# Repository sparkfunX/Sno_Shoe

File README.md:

# Snō Shoe

A Qwiic, USB-C and HDMI breakout board for the [Alorium Technology Snō](https://www.sparkfun.com/products/15145)

The Alorium Technologies Snō is based on the Intel MAX 10 10M16SAU169C8G FPGA. It includes an ATmega328-compatible microcontroller core
which appears as an Arduino Uno and can be configured as normal through the Arduino IDE. It supports Serial, I<sup>2</sup>C and all the usual
Uno features.

The Snō Shoe makes it easy to connect to the Snō over:
- USB-C (instead of needing to use an FTDI adapter)
- HDMI
- Qwiic (I<sup>2</sup>C)

Paul has written an "Xcelerator Block" for the Snō which produces VGA text and graphics over HDMI. The assembled Snō Shoe is essentially an
Arduino-programmable Serial & Qwiic VGA Adapter.

- https://github.com/PaulZC/XLR8_VGA_HDMI_XB

## Repository Contents

- **/Hardware** - Eagle PCB, SCH and LBR design files
- **[LICENSE.md](./LICENSE.md)** contains the licence information

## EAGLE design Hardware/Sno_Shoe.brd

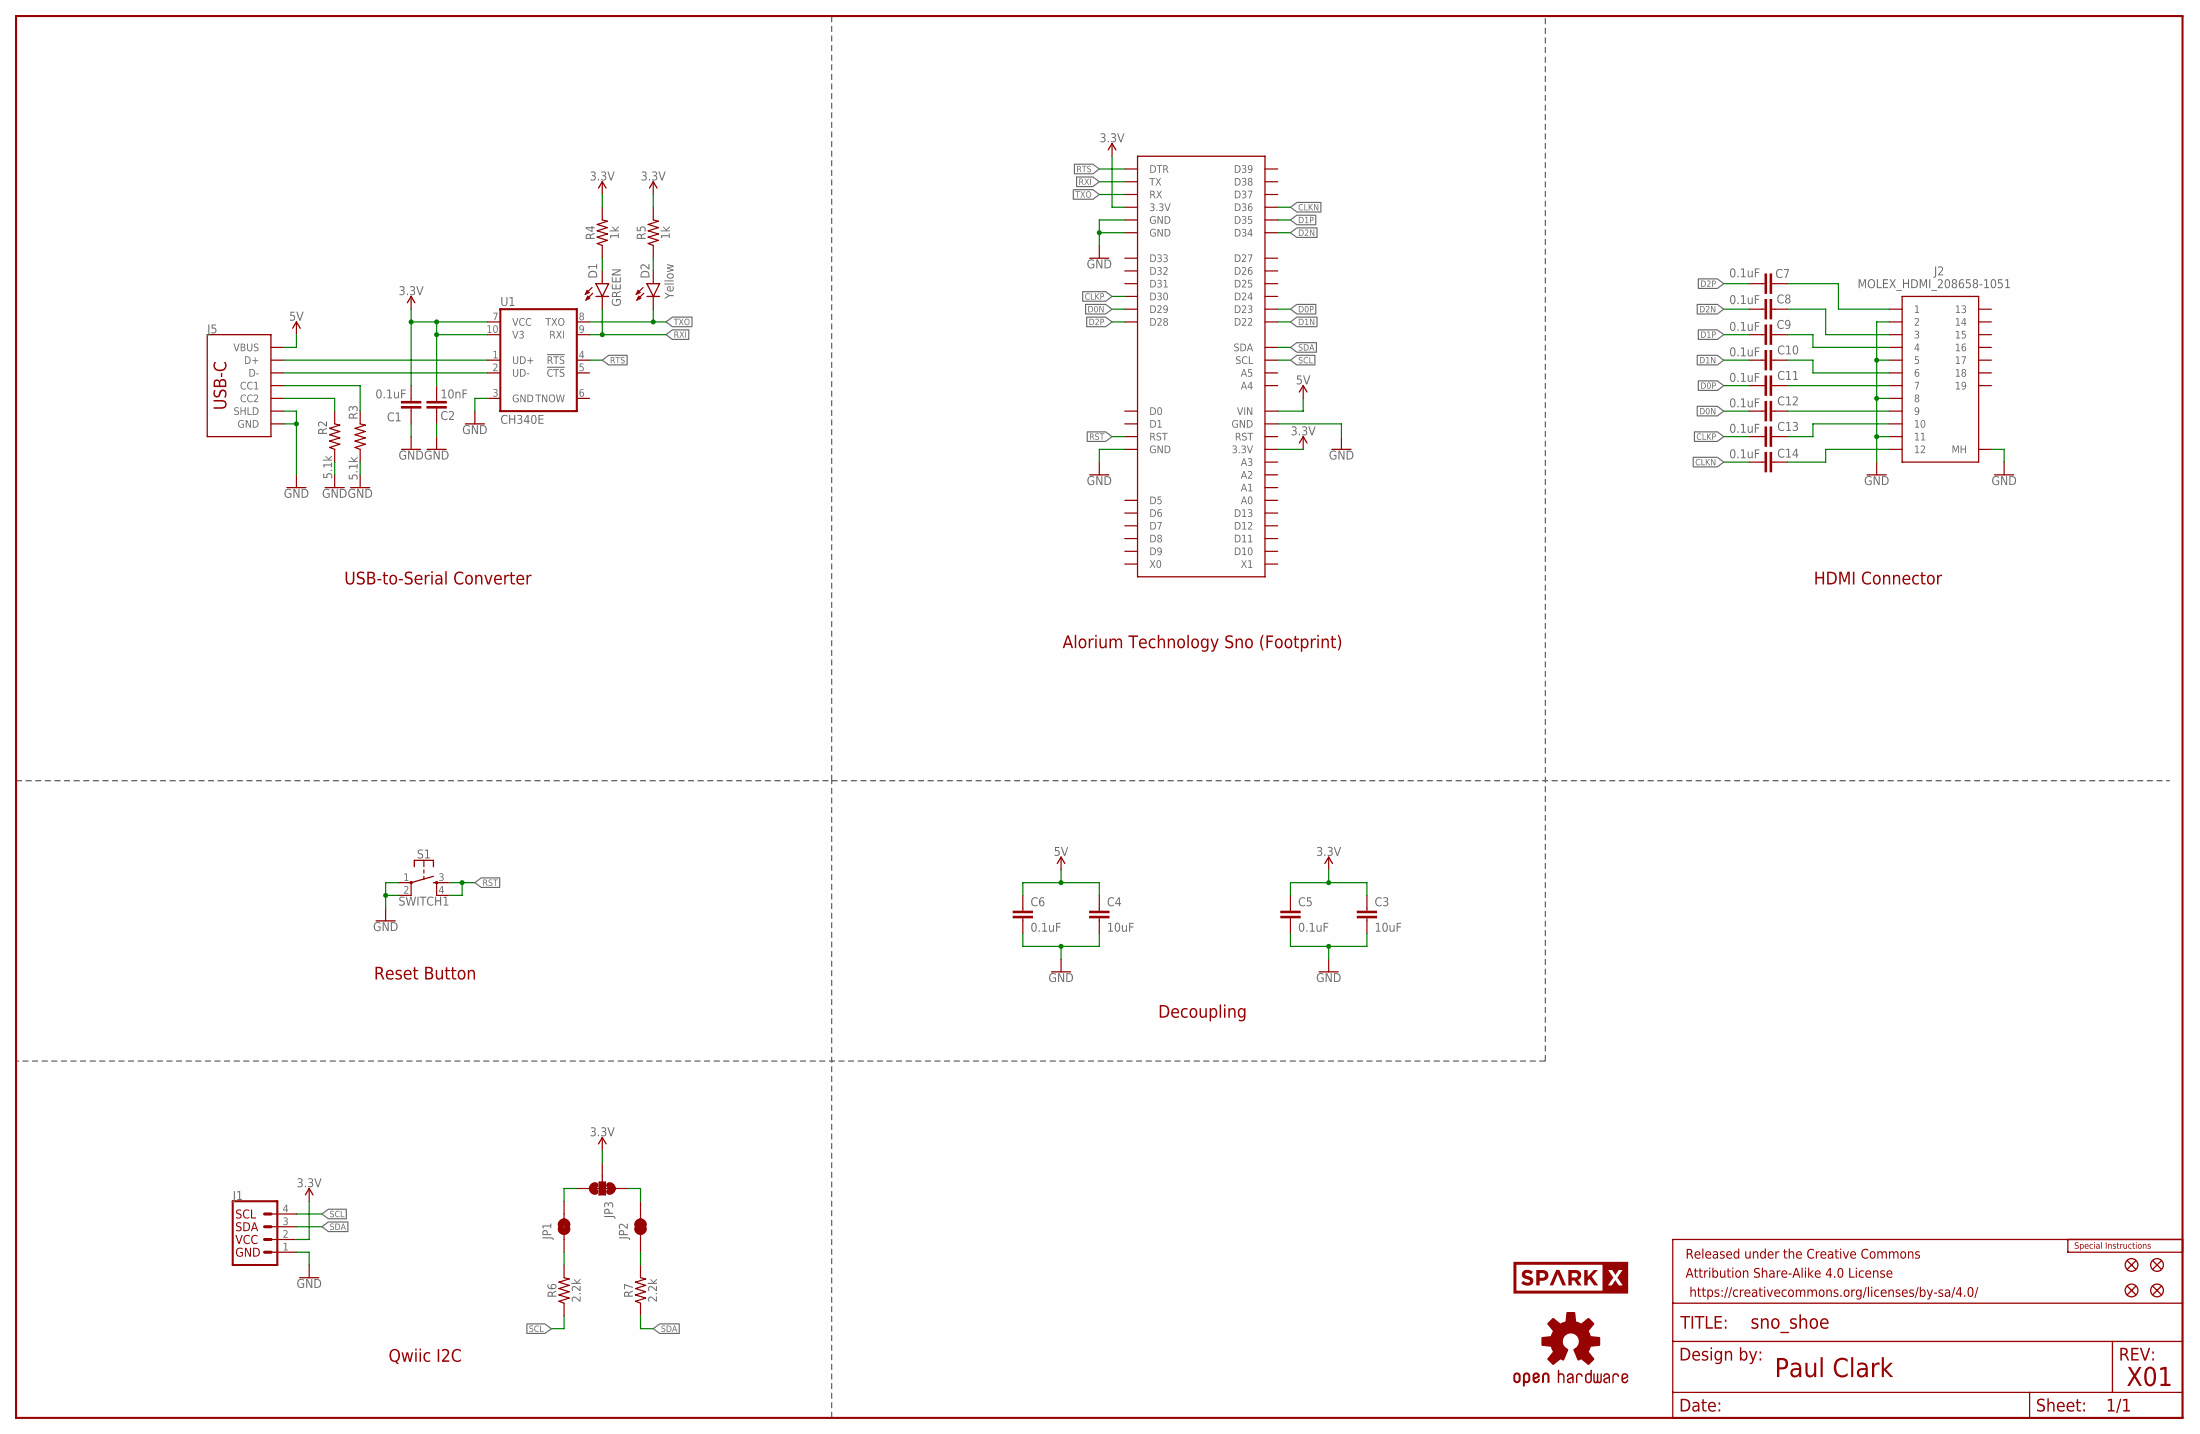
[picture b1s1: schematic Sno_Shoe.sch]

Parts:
C1, C5, C6, C7, C8, C9, C10, C11, C12, C13, C14: 0.1uF; 0402-TIGHT
C2: 10nF; 0402-TIGHT
C3: 10uF; 0402-TIGHT
C4: 10uF; 0805
D1: GREEN; LED-0603
D2: Yellow; LED-0603
FD1, FD2, FD3, FD4: FIDUCIAL1X2; FIDUCIAL-1X2
FRAME1: FRAME-LEDGER; CREATIVE_COMMONS
J1: QWIIC_RIGHT_ANGLE; JST04_1MM_RA
J2: MOLEX_HDMI_208658-1051
J5: USB_C_4-LAYER_PADS; USB-C-16P_4LAYER-PADS
JP1, JP2: JUMPER-SMT_2_NC_TRACE_SILK; SMT-JUMPER_2_NC_TRACE_SILK
JP3: JUMPER-SMT_3_2-NC_TRACE_SILK; SMT-JUMPER_3_2-NC_TRACE_SILK
LOGO1: SPECIAL_INSTRUCTIONS-ORDERING; ORDERING_INSTRUCTIONS
LOGO2: OSHW-LOGOMINI; OSHW-LOGO-MINI
R2, R3: 5.1k; 0402-TIGHT
R4, R5: 1k; 0402-TIGHT
R6, R7: 2.2k; 0402-TIGHT
S1: SWITCH1; TACTILE_SWITCH_SMD_5.2MM
SPARKX2: SPARKX-LOGO4; SPARKX-MEDIUM
U1: CH340E; MSOP10
U$1: SNO_MISSING_PINS

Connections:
3.3V: C1.1, C2.1, C3.1, C5.1, J1.2, JP3.2, R4.2, R5.2, U1.7 (VCC), U1.10 (V3), U$1.P$28 (3.3V), U$1.P$56 (3.3V)
5V: C4.1, C6.1, J5.VBUS1 (VBUS), J5.VBUS2 (VBUS), U$1.P$31 (VIN)
CC3: J5.B5 (CC2), R2.2
CC4: J5.A5 (CC1), R3.2
CLKN: C14.1, U$1.P$50 (D36)
CLKP: C13.1, U$1.P$44 (D30)
D0N: C12.1, U$1.P$43 (D29)
D0P: C11.1, U$1.P$37 (D23)
D1N: C10.1, U$1.P$36 (D22)
D1P: C9.1, U$1.P$49 (D35)
D2N: C8.1, U$1.P$48 (D34)
D2P: C7.1, U$1.P$42 (D28)
D+2: J5.A6 (D+), J5.B6 (D+), U1.1 (UD+)
D-2: J5.A7 (D-), J5.B7 (D-), U1.2 (UD-)
GND: C1.2, C2.2, C3.2, C4.2, C5.2, C6.2, J1.1, J2.2, J2.5, J2.8, J2.11, J2.MH1 (MH), J2.MH2 (MH), J2.MH3 (MH), J2.MH4 (MH), J5.GND, J5.GND2 (GND), J5.SHLD1 (SHLD), J5.SHLD2 (SHLD), J5.SHLD3 (SHLD), J5.SHLD4 (SHLD), R2.1, R3.1, S1.1, S1.2, U1.3 (GND), U$1.P$4 (GND), U$1.P$30 (GND), U$1.P$54 (GND), U$1.P$55 (GND)
unnamed: JP2.2, JP3.1
unnamed: JP1.2, JP3.3
unnamed: JP1.1, R6.2
unnamed: JP2.1, R7.2
unnamed: C7.2, J2.1
unnamed: C8.2, J2.3
unnamed: C9.2, J2.4
unnamed: C10.2, J2.6
unnamed: C11.2, J2.7
unnamed: C12.2, J2.9
unnamed: C13.2, J2.10
unnamed: C14.2, J2.12
unnamed: D1.A, R4.1
unnamed: D2.A, R5.1
RST: S1.3, S1.4, U$1.P$3 (RST)
RTS: U1.4 (!RTS), U$1.P$59 (DTR)
RXI: D1.C, U1.9 (RXI), U$1.P$58 (TX)
SCL: J1.4, R6.1, U$1.P$34 (SCL)
SDA: J1.3, R7.1, U$1.P$35 (SDA)
TXO: D2.C, U1.8 (TXO), U$1.P$57 (RX)

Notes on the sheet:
USB-to-Serial Converter
Alorium Technology Sno (Footprint)
HDMI Connector
Reset Button
Qwiic I2C
Decoupling
Paul Clark
X01

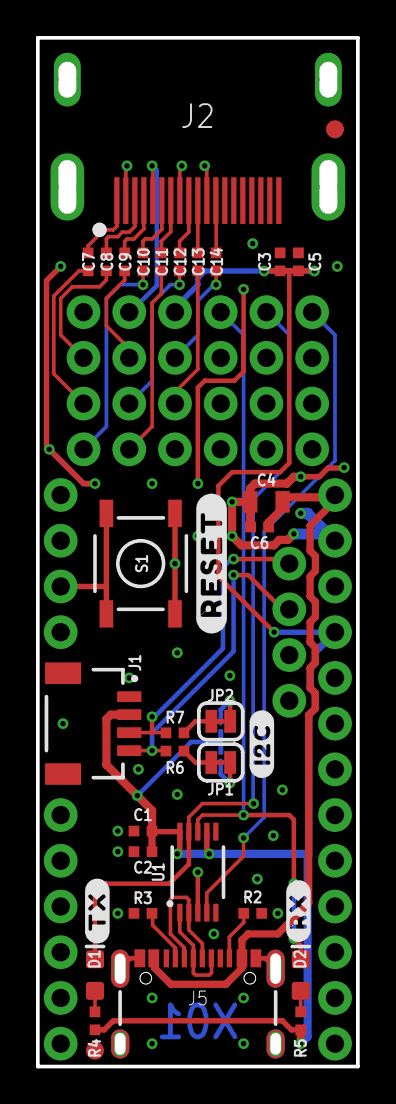
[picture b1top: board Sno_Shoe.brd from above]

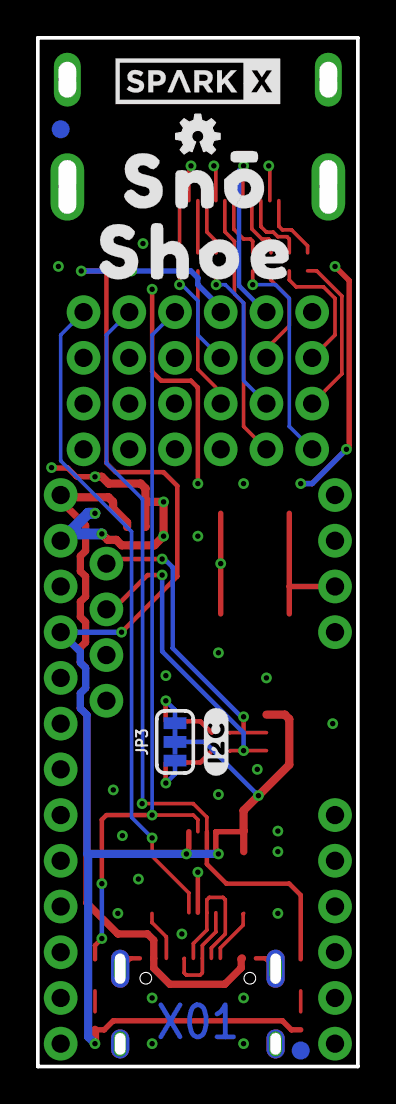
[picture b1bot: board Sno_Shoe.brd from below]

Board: 2 copper layers, 17.0 x 56.4 mm, 47 parts (9 on the bottom side), 35 nets.

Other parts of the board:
U$2: SNO0
U$3: SHOE0
U$4: #0
U$5: #RESET#0
U$6, U$7: #I2C#0
U$8: #TX#0
U$9: #RX#0

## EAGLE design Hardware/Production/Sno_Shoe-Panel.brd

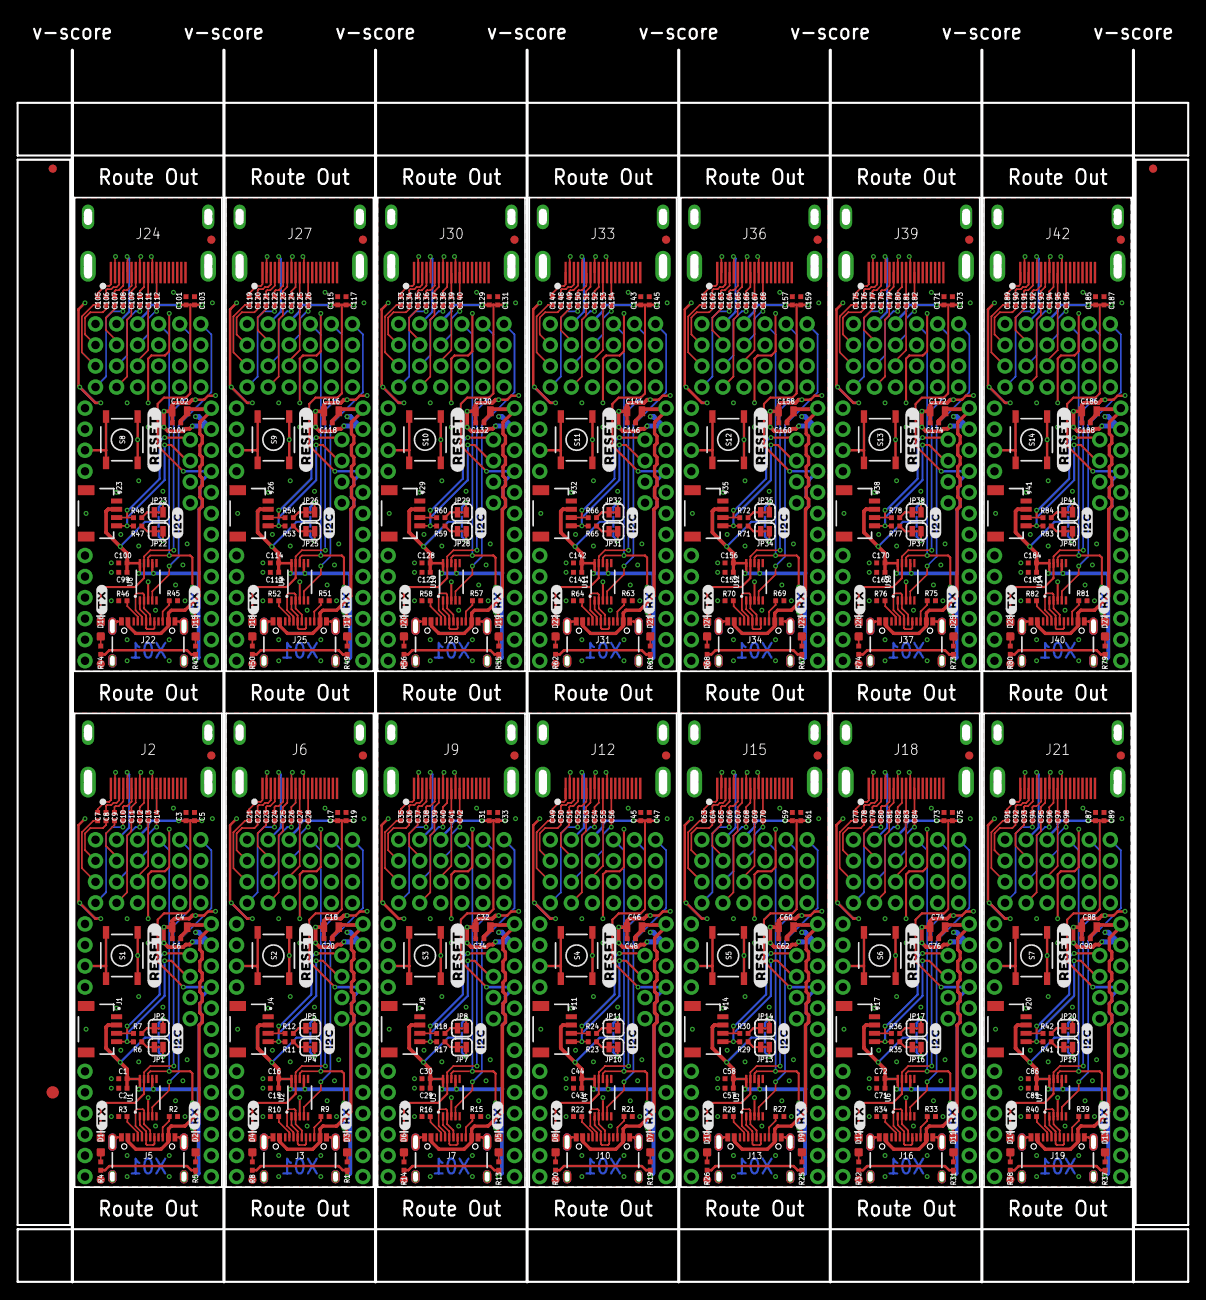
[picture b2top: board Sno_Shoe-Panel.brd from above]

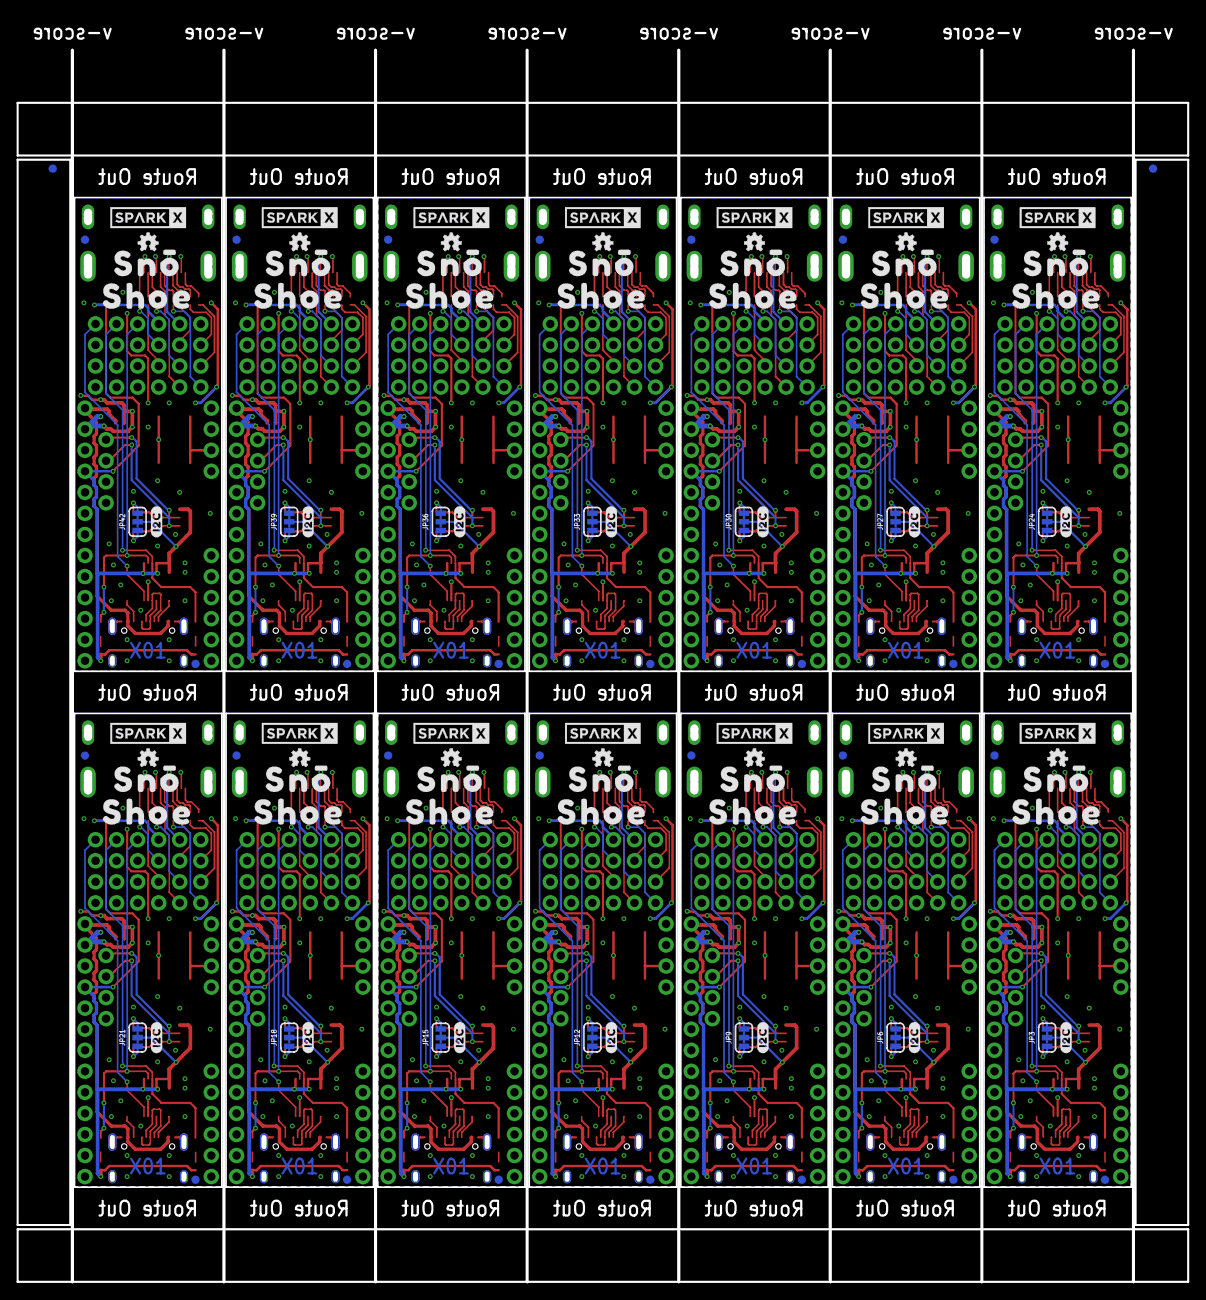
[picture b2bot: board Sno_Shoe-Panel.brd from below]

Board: 2 copper layers, 140.5 x 151.8 mm, 635 parts (128 on the bottom side), 490 nets.

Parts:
C1, C5, C6, C7, C8, C9, C10, C11, C12, C13, C14, C16, C19, C20, C21, C22, C23, C24, C25, C26, C27, C28, C30, C33, C34, C35, C36, C37, C38, C39, C40, C41, C42, C44, C47, C48, C49, C50, C51, C52, C53, C54, C55, C56, C58, C61, C62, C63, C64, C65, C66, C67, C68, C69, C70, C72, C75, C76, C77, C78, C79, C80, C81, C82, C83, C84, C86, C89, C90, C91, C92, C93, C94, C95, C96, C97, C98, C100, C103, C104, C105, C106, C107, C108, C109, C110, C111, C112, C114, C117, C118, C119, C120, C121, C122, C123, C124, C125, C126, C128, C131, C132, C133, C134, C135, C136, C137, C138, C139, C140, C142, C145, C146, C147, C148, C149, C150, C151, C152, C153, C154, C156, C159, C160, C161, C162, C163, C164, C165, C166, C167, C168, C170, C173, C174, C175, C176, C177, C178, C179, C180, C181, C182, C184, C187, C188, C189, C190, C191, C192, C193, C194, C195, C196: 0.1uF; 0402-TIGHT
C2, C15, C29, C43, C57, C71, C85, C99, C113, C127, C141, C155, C169, C183: 10nF; 0402-TIGHT
C3, C17, C31, C45, C59, C73, C87, C101, C115, C129, C143, C157, C171, C185: 10uF; 0402-TIGHT
C4, C18, C32, C46, C60, C74, C88, C102, C116, C130, C144, C158, C172, C186: 10uF; 0805
D1, D4, D6, D8, D10, D12, D14, D16, D18, D20, D22, D24, D26, D28: GREEN; LED-0603
D2, D3, D5, D7, D9, D11, D13, D15, D17, D19, D21, D23, D25, D27: Yellow; LED-0603
E$1, E$2, E$3, E$4: FIDUCIAL-1X2
E$5: FIDUCIAL-1.5X3
FD1, FD2, FD3, FD4, FD5, FD6, FD7, FD8, FD9, FD10, FD11, FD12, FD13, FD14, FD15, FD16, FD17, FD18, FD19, FD20, FD21, FD22, FD23, FD24, FD25, FD26, FD27, FD28, FD29, FD30, FD31, FD32, FD33, FD34, FD35, FD36, FD37, FD38, FD39, FD40, FD41, FD42, FD43, FD44, FD45, FD46, FD47, FD48, FD49, FD50, FD51, FD52, FD53, FD54, FD55, FD56: FIDUCIAL1X2; FIDUCIAL-1X2
J1, J4, J8, J11, J14, J17, J20, J23, J26, J29, J32, J35, J38, J41: QWIIC_RIGHT_ANGLE; JST04_1MM_RA
J2, J6, J9, J12, J15, J18, J21, J24, J27, J30, J33, J36, J39, J42: MOLEX_HDMI_208658-1051
J3, J5, J7, J10, J13, J16, J19, J22, J25, J28, J31, J34, J37, J40: USB-C-16P_4LAYER-PADS
JP1, JP2, JP4, JP5, JP7, JP8, JP10, JP11, JP13, JP14, JP16, JP17, JP19, JP20, JP22, JP23, JP25, JP26, JP28, JP29, JP31, JP32, JP34, JP35, JP37, JP38, JP40, JP41: JUMPER-SMT_2_NC_TRACE_SILK; SMT-JUMPER_2_NC_TRACE_SILK
JP3, JP6, JP9, JP12, JP15, JP18, JP21, JP24, JP27, JP30, JP33, JP36, JP39, JP42: JUMPER-SMT_3_2-NC_TRACE_SILK; SMT-JUMPER_3_2-NC_TRACE_SILK
LOGO1, LOGO2, LOGO3, LOGO4, LOGO5, LOGO6, LOGO7, LOGO8, LOGO9, LOGO10, LOGO11, LOGO12, LOGO13, LOGO14: OSHW-LOGOMINI; OSHW-LOGO-MINI
R1, R4, R5, R8, R13, R14, R19, R20, R25, R26, R31, R32, R37, R38, R43, R44, R49, R50, R55, R56, R61, R62, R67, R68, R73, R74, R79, R80: 1k; 0402-TIGHT
R2, R3, R9, R10, R15, R16, R21, R22, R27, R28, R33, R34, R39, R40, R45, R46, R51, R52, R57, R58, R63, R64, R69, R70, R75, R76, R81, R82: 5.1k; 0402-TIGHT
R6, R7, R11, R12, R17, R18, R23, R24, R29, R30, R35, R36, R41, R42, R47, R48, R53, R54, R59, R60, R65, R66, R71, R72, R77, R78, R83, R84: 2.2k; 0402-TIGHT
S1, S2, S3, S4, S5, S6, S7, S8, S9, S10, S11, S12, S13, S14: SWITCH1; TACTILE_SWITCH_SMD_5.2MM
SPARKX1, SPARKX2, SPARKX3, SPARKX4, SPARKX5, SPARKX6, SPARKX7, SPARKX8, SPARKX9, SPARKX10, SPARKX11, SPARKX12, SPARKX13, SPARKX14: SPARKX-LOGO4; SPARKX-MEDIUM
U1, U2, U3, U4, U5, U6, U7, U8, U9, U10, U11, U12, U13, U14: CH340E; MSOP10
U$1, U$10, U$19, U$28, U$37, U$46, U$55, U$64, U$73, U$82, U$91, U$100, U$109, U$118: SNO_MISSING_PINS
U$2, U$11, U$20, U$29, U$38, U$47, U$56, U$65, U$74, U$83, U$92, U$101, U$110, U$119: SNO0
U$3, U$12, U$21, U$30, U$39, U$48, U$57, U$66, U$75, U$84, U$93, U$102, U$111, U$120: SHOE0
U$4, U$13, U$22, U$31, U$40, U$49, U$58, U$67, U$76, U$85, U$94, U$103, U$112, U$121: #0
U$5, U$14, U$23, U$32, U$41, U$50, U$59, U$68, U$77, U$86, U$95, U$104, U$113, U$122: #RESET#0
U$6, U$7, U$15, U$16, U$24, U$25, U$33, U$34, U$42, U$43, U$51, U$52, U$60, U$61, U$69, U$70, U$78, U$79, U$87, U$88, U$96, U$97, U$105, U$106, U$114, U$115, U$123, U$124: #I2C#0
U$8, U$17, U$26, U$35, U$44, U$53, U$62, U$71, U$80, U$89, U$98, U$107, U$116, U$125: #TX#0
U$9, U$18, U$27, U$36, U$45, U$54, U$63, U$72, U$81, U$90, U$99, U$108, U$117, U$126: #RX#0

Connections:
3.3V: C1.1, C2.1, C3.1, C5.1, J1.2, JP3.2, R4.2, R5.2, U1.7, U1.10, U$1.P$28, U$1.P$56
3.3V1: C15.1, C16.1, C17.1, C19.1, J4.2, JP6.2, R1.2, R8.2, U2.7, U2.10, U$10.P$28, U$10.P$56
3.3V2: C29.1, C30.1, C31.1, C33.1, J8.2, JP9.2, R13.2, R14.2, U3.7, U3.10, U$19.P$28, U$19.P$56
3.3V3: C43.1, C44.1, C45.1, C47.1, J11.2, JP12.2, R19.2, R20.2, U4.7, U4.10, U$28.P$28, U$28.P$56
3.3V4: C57.1, C58.1, C59.1, C61.1, J14.2, JP15.2, R25.2, R26.2, U5.7, U5.10, U$37.P$28, U$37.P$56
3.3V5: C71.1, C72.1, C73.1, C75.1, J17.2, JP18.2, R31.2, R32.2, U6.7, U6.10, U$46.P$28, U$46.P$56
3.3V6: C85.1, C86.1, C87.1, C89.1, J20.2, JP21.2, R37.2, R38.2, U7.7, U7.10, U$55.P$28, U$55.P$56
3.3V7: C99.1, C100.1, C101.1, C103.1, J23.2, JP24.2, R43.2, R44.2, U8.7, U8.10, U$64.P$28, U$64.P$56
3.3V8: C113.1, C114.1, C115.1, C117.1, J26.2, JP27.2, R49.2, R50.2, U9.7, U9.10, U$73.P$28, U$73.P$56
3.3V9: C127.1, C128.1, C129.1, C131.1, J29.2, JP30.2, R55.2, R56.2, U10.7, U10.10, U$82.P$28, U$82.P$56
3.3V10: C141.1, C142.1, C143.1, C145.1, J32.2, JP33.2, R61.2, R62.2, U11.7, U11.10, U$91.P$28, U$91.P$56
3.3V11: C155.1, C156.1, C157.1, C159.1, J35.2, JP36.2, R67.2, R68.2, U12.7, U12.10, U$100.P$28, U$100.P$56
3.3V12: C169.1, C170.1, C171.1, C173.1, J38.2, JP39.2, R73.2, R74.2, U13.7, U13.10, U$109.P$28, U$109.P$56
3.3V13: C183.1, C184.1, C185.1, C187.1, J41.2, JP42.2, R79.2, R80.2, U14.7, U14.10, U$118.P$28, U$118.P$56
5V: C4.1, C6.1, J5.VBUS1, J5.VBUS2, U$1.P$31
5V1: C18.1, C20.1, J3.VBUS1, J3.VBUS2, U$10.P$31
5V2: C32.1, C34.1, J7.VBUS1, J7.VBUS2, U$19.P$31
5V3: C46.1, C48.1, J10.VBUS1, J10.VBUS2, U$28.P$31
5V4: C60.1, C62.1, J13.VBUS1, J13.VBUS2, U$37.P$31
5V5: C74.1, C76.1, J16.VBUS1, J16.VBUS2, U$46.P$31
5V6: C88.1, C90.1, J19.VBUS1, J19.VBUS2, U$55.P$31
5V7: C102.1, C104.1, J22.VBUS1, J22.VBUS2, U$64.P$31
5V8: C116.1, C118.1, J25.VBUS1, J25.VBUS2, U$73.P$31
5V9: C130.1, C132.1, J28.VBUS1, J28.VBUS2, U$82.P$31
5V10: C144.1, C146.1, J31.VBUS1, J31.VBUS2, U$91.P$31
5V11: C158.1, C160.1, J34.VBUS1, J34.VBUS2, U$100.P$31
5V12: C172.1, C174.1, J37.VBUS1, J37.VBUS2, U$109.P$31
5V13: C186.1, C188.1, J40.VBUS1, J40.VBUS2, U$118.P$31
CC1: J3.B5, R9.2
CC2: J3.A5, R10.2
CC3: J5.B5, R2.2
CC4: J5.A5, R3.2
CC5: J7.B5, R15.2
CC6: J7.A5, R16.2
CC7: J10.B5, R21.2
CC8: J10.A5, R22.2
CC9: J13.B5, R27.2
CC10: J13.A5, R28.2
CC11: J16.B5, R33.2
CC12: J16.A5, R34.2
CC13: J19.B5, R39.2
CC14: J19.A5, R40.2
CC15: J22.B5, R45.2
CC16: J22.A5, R46.2
CC17: J25.B5, R51.2
CC18: J25.A5, R52.2
CC19: J28.B5, R57.2
CC20: J28.A5, R58.2
CC21: J31.B5, R63.2
CC22: J31.A5, R64.2
CC23: J34.B5, R69.2
CC24: J34.A5, R70.2
CC25: J37.B5, R75.2
CC26: J37.A5, R76.2
CC27: J40.B5, R81.2
CC28: J40.A5, R82.2
CLKN: C14.1, U$1.P$50
CLKN1: C28.1, U$10.P$50
CLKN2: C42.1, U$19.P$50
CLKN3: C56.1, U$28.P$50
CLKN4: C70.1, U$37.P$50
CLKN5: C84.1, U$46.P$50
CLKN6: C98.1, U$55.P$50
CLKN7: C112.1, U$64.P$50
CLKN8: C126.1, U$73.P$50
CLKN9: C140.1, U$82.P$50
CLKN10: C154.1, U$91.P$50
CLKN11: C168.1, U$100.P$50
CLKN12: C182.1, U$109.P$50
CLKN13: C196.1, U$118.P$50
CLKP: C13.1, U$1.P$44
CLKP1: C27.1, U$10.P$44
CLKP2: C41.1, U$19.P$44
CLKP3: C55.1, U$28.P$44
CLKP4: C69.1, U$37.P$44
CLKP5: C83.1, U$46.P$44
CLKP6: C97.1, U$55.P$44
CLKP7: C111.1, U$64.P$44
CLKP8: C125.1, U$73.P$44
CLKP9: C139.1, U$82.P$44
CLKP10: C153.1, U$91.P$44
CLKP11: C167.1, U$100.P$44
CLKP12: C181.1, U$109.P$44
CLKP13: C195.1, U$118.P$44
D0N: C12.1, U$1.P$43
D0N1: C26.1, U$10.P$43
D0N2: C40.1, U$19.P$43
D0N3: C54.1, U$28.P$43
D0N4: C68.1, U$37.P$43
D0N5: C82.1, U$46.P$43
D0N6: C96.1, U$55.P$43
D0N7: C110.1, U$64.P$43
D0N8: C124.1, U$73.P$43
D0N9: C138.1, U$82.P$43
D0N10: C152.1, U$91.P$43
D0N11: C166.1, U$100.P$43
D0N12: C180.1, U$109.P$43
D0N13: C194.1, U$118.P$43
D0P: C11.1, U$1.P$37
D0P1: C25.1, U$10.P$37
D0P2: C39.1, U$19.P$37
D0P3: C53.1, U$28.P$37
D0P4: C67.1, U$37.P$37
D0P5: C81.1, U$46.P$37
D0P6: C95.1, U$55.P$37
D0P7: C109.1, U$64.P$37
D0P8: C123.1, U$73.P$37
D0P9: C137.1, U$82.P$37
D0P10: C151.1, U$91.P$37
D0P11: C165.1, U$100.P$37
D0P12: C179.1, U$109.P$37
D0P13: C193.1, U$118.P$37
D1N: C10.1, U$1.P$36
D1N1: C24.1, U$10.P$36
D1N2: C38.1, U$19.P$36
D1N3: C52.1, U$28.P$36
D1N4: C66.1, U$37.P$36
D1N5: C80.1, U$46.P$36
D1N6: C94.1, U$55.P$36
D1N7: C108.1, U$64.P$36
D1N8: C122.1, U$73.P$36
D1N9: C136.1, U$82.P$36
D1N10: C150.1, U$91.P$36
D1N11: C164.1, U$100.P$36
D1N12: C178.1, U$109.P$36
D1N13: C192.1, U$118.P$36
D1P: C9.1, U$1.P$49
D1P1: C23.1, U$10.P$49
D1P2: C37.1, U$19.P$49
D1P3: C51.1, U$28.P$49
D1P4: C65.1, U$37.P$49
D1P5: C79.1, U$46.P$49
D1P6: C93.1, U$55.P$49
D1P7: C107.1, U$64.P$49
D1P8: C121.1, U$73.P$49
D1P9: C135.1, U$82.P$49
D1P10: C149.1, U$91.P$49
D1P11: C163.1, U$100.P$49
D1P12: C177.1, U$109.P$49
D1P13: C191.1, U$118.P$49
D2N: C8.1, U$1.P$48
D2N1: C22.1, U$10.P$48
D2N2: C36.1, U$19.P$48
D2N3: C50.1, U$28.P$48
D2N4: C64.1, U$37.P$48
D2N5: C78.1, U$46.P$48
D2N6: C92.1, U$55.P$48
D2N7: C106.1, U$64.P$48
D2N8: C120.1, U$73.P$48
D2N9: C134.1, U$82.P$48
D2N10: C148.1, U$91.P$48
D2N11: C162.1, U$100.P$48
D2N12: C176.1, U$109.P$48
D2N13: C190.1, U$118.P$48
D2P: C7.1, U$1.P$42
D2P1: C21.1, U$10.P$42
D2P2: C35.1, U$19.P$42
D2P3: C49.1, U$28.P$42
D2P4: C63.1, U$37.P$42
D2P5: C77.1, U$46.P$42
D2P6: C91.1, U$55.P$42
D2P7: C105.1, U$64.P$42
D2P8: C119.1, U$73.P$42
D2P9: C133.1, U$82.P$42
D2P10: C147.1, U$91.P$42
D2P11: C161.1, U$100.P$42
D2P12: C175.1, U$109.P$42
D2P13: C189.1, U$118.P$42
D+1: J3.A6, J3.B6, U2.1
D+2: J5.A6, J5.B6, U1.1
D+3: J7.A6, J7.B6, U3.1
D+4: J10.A6, J10.B6, U4.1
D+5: J13.A6, J13.B6, U5.1
D+6: J16.A6, J16.B6, U6.1
D+7: J19.A6, J19.B6, U7.1
D+8: J22.A6, J22.B6, U8.1
D+9: J25.A6, J25.B6, U9.1
D+10: J28.A6, J28.B6, U10.1
D+11: J31.A6, J31.B6, U11.1
D+12: J34.A6, J34.B6, U12.1
D+13: J37.A6, J37.B6, U13.1
D+14: J40.A6, J40.B6, U14.1
D-1: J3.A7, J3.B7, U2.2
D-2: J5.A7, J5.B7, U1.2
D-3: J7.A7, J7.B7, U3.2
D-4: J10.A7, J10.B7, U4.2
D-5: J13.A7, J13.B7, U5.2
D-6: J16.A7, J16.B7, U6.2
D-7: J19.A7, J19.B7, U7.2
D-8: J22.A7, J22.B7, U8.2
D-9: J25.A7, J25.B7, U9.2
D-10: J28.A7, J28.B7, U10.2
D-11: J31.A7, J31.B7, U11.2
D-12: J34.A7, J34.B7, U12.2
D-13: J37.A7, J37.B7, U13.2
D-14: J40.A7, J40.B7, U14.2
GND: C1.2, C2.2, C3.2, C4.2, C5.2, C6.2, J1.1, J2.2, J2.5, J2.8, J2.11, J2.MH1, J2.MH2, J2.MH3, J2.MH4, J5.GND, J5.GND2, J5.SHLD1, J5.SHLD2, J5.SHLD3, J5.SHLD4, R2.1, R3.1, S1.1, S1.2, U1.3, U$1.P$4, U$1.P$30, U$1.P$54, U$1.P$55
GND1: C15.2, C16.2, C17.2, C18.2, C19.2, C20.2, J3.GND, J3.GND2, J3.SHLD1, J3.SHLD2, J3.SHLD3, J3.SHLD4, J4.1, J6.2, J6.5, J6.8, J6.11, J6.MH1, J6.MH2, J6.MH3, J6.MH4, R9.1, R10.1, S2.1, S2.2, U2.3, U$10.P$4, U$10.P$30, U$10.P$54, U$10.P$55
GND2: C29.2, C30.2, C31.2, C32.2, C33.2, C34.2, J7.GND, J7.GND2, J7.SHLD1, J7.SHLD2, J7.SHLD3, J7.SHLD4, J8.1, J9.2, J9.5, J9.8, J9.11, J9.MH1, J9.MH2, J9.MH3, J9.MH4, R15.1, R16.1, S3.1, S3.2, U3.3, U$19.P$4, U$19.P$30, U$19.P$54, U$19.P$55
GND3: C43.2, C44.2, C45.2, C46.2, C47.2, C48.2, J10.GND, J10.GND2, J10.SHLD1, J10.SHLD2, J10.SHLD3, J10.SHLD4, J11.1, J12.2, J12.5, J12.8, J12.11, J12.MH1, J12.MH2, J12.MH3, J12.MH4, R21.1, R22.1, S4.1, S4.2, U4.3, U$28.P$4, U$28.P$30, U$28.P$54, U$28.P$55
GND4: C57.2, C58.2, C59.2, C60.2, C61.2, C62.2, J13.GND, J13.GND2, J13.SHLD1, J13.SHLD2, J13.SHLD3, J13.SHLD4, J14.1, J15.2, J15.5, J15.8, J15.11, J15.MH1, J15.MH2, J15.MH3, J15.MH4, R27.1, R28.1, S5.1, S5.2, U5.3, U$37.P$4, U$37.P$30, U$37.P$54, U$37.P$55
GND5: C71.2, C72.2, C73.2, C74.2, C75.2, C76.2, J16.GND, J16.GND2, J16.SHLD1, J16.SHLD2, J16.SHLD3, J16.SHLD4, J17.1, J18.2, J18.5, J18.8, J18.11, J18.MH1, J18.MH2, J18.MH3, J18.MH4, R33.1, R34.1, S6.1, S6.2, U6.3, U$46.P$4, U$46.P$30, U$46.P$54, U$46.P$55
GND6: C85.2, C86.2, C87.2, C88.2, C89.2, C90.2, J19.GND, J19.GND2, J19.SHLD1, J19.SHLD2, J19.SHLD3, J19.SHLD4, J20.1, J21.2, J21.5, J21.8, J21.11, J21.MH1, J21.MH2, J21.MH3, J21.MH4, R39.1, R40.1, S7.1, S7.2, U7.3, U$55.P$4, U$55.P$30, U$55.P$54, U$55.P$55
GND7: C99.2, C100.2, C101.2, C102.2, C103.2, C104.2, J22.GND, J22.GND2, J22.SHLD1, J22.SHLD2, J22.SHLD3, J22.SHLD4, J23.1, J24.2, J24.5, J24.8, J24.11, J24.MH1, J24.MH2, J24.MH3, J24.MH4, R45.1, R46.1, S8.1, S8.2, U8.3, U$64.P$4, U$64.P$30, U$64.P$54, U$64.P$55
GND8: C113.2, C114.2, C115.2, C116.2, C117.2, C118.2, J25.GND, J25.GND2, J25.SHLD1, J25.SHLD2, J25.SHLD3, J25.SHLD4, J26.1, J27.2, J27.5, J27.8, J27.11, J27.MH1, J27.MH2, J27.MH3, J27.MH4, R51.1, R52.1, S9.1, S9.2, U9.3, U$73.P$4, U$73.P$30, U$73.P$54, U$73.P$55
GND9: C127.2, C128.2, C129.2, C130.2, C131.2, C132.2, J28.GND, J28.GND2, J28.SHLD1, J28.SHLD2, J28.SHLD3, J28.SHLD4, J29.1, J30.2, J30.5, J30.8, J30.11, J30.MH1, J30.MH2, J30.MH3, J30.MH4, R57.1, R58.1, S10.1, S10.2, U10.3, U$82.P$4, U$82.P$30, U$82.P$54, U$82.P$55
GND10: C141.2, C142.2, C143.2, C144.2, C145.2, C146.2, J31.GND, J31.GND2, J31.SHLD1, J31.SHLD2, J31.SHLD3, J31.SHLD4, J32.1, J33.2, J33.5, J33.8, J33.11, J33.MH1, J33.MH2, J33.MH3, J33.MH4, R63.1, R64.1, S11.1, S11.2, U11.3, U$91.P$4, U$91.P$30, U$91.P$54, U$91.P$55
GND11: C155.2, C156.2, C157.2, C158.2, C159.2, C160.2, J34.GND, J34.GND2, J34.SHLD1, J34.SHLD2, J34.SHLD3, J34.SHLD4, J35.1, J36.2, J36.5, J36.8, J36.11, J36.MH1, J36.MH2, J36.MH3, J36.MH4, R69.1, R70.1, S12.1, S12.2, U12.3, U$100.P$4, U$100.P$30, U$100.P$54, U$100.P$55
GND12: C169.2, C170.2, C171.2, C172.2, C173.2, C174.2, J37.GND, J37.GND2, J37.SHLD1, J37.SHLD2, J37.SHLD3, J37.SHLD4, J38.1, J39.2, J39.5, J39.8, J39.11, J39.MH1, J39.MH2, J39.MH3, J39.MH4, R75.1, R76.1, S13.1, S13.2, U13.3, U$109.P$4, U$109.P$30, U$109.P$54, U$109.P$55
GND13: C183.2, C184.2, C185.2, C186.2, C187.2, C188.2, J40.GND, J40.GND2, J40.SHLD1, J40.SHLD2, J40.SHLD3, J40.SHLD4, J41.1, J42.2, J42.5, J42.8, J42.11, J42.MH1, J42.MH2, J42.MH3, J42.MH4, R81.1, R82.1, S14.1, S14.2, U14.3, U$118.P$4, U$118.P$30, U$118.P$54, U$118.P$55
unnamed: D4.A, R8.1
unnamed: JP2.2, JP3.1
unnamed: JP1.2, JP3.3
unnamed: JP1.1, R6.2
unnamed: JP2.1, R7.2
unnamed: C7.2, J2.1
unnamed: C8.2, J2.3
unnamed: C9.2, J2.4
unnamed: C10.2, J2.6
unnamed: C11.2, J2.7
unnamed: C12.2, J2.9
unnamed: C13.2, J2.10
unnamed: C14.2, J2.12
unnamed: D3.A, R1.1
unnamed: JP5.2, JP6.1
unnamed: JP4.2, JP6.3
unnamed: JP4.1, R11.2
unnamed: JP5.1, R12.2
unnamed: C21.2, J6.1
unnamed: C22.2, J6.3
unnamed: C23.2, J6.4
unnamed: C24.2, J6.6
unnamed: C25.2, J6.7
unnamed: C26.2, J6.9
unnamed: C27.2, J6.10
unnamed: D1.A, R4.1
unnamed: D2.A, R5.1
unnamed: C28.2, J6.12
unnamed: D6.A, R14.1
unnamed: D5.A, R13.1
unnamed: JP8.2, JP9.1
unnamed: JP7.2, JP9.3
unnamed: JP7.1, R17.2
unnamed: JP8.1, R18.2
unnamed: C35.2, J9.1
unnamed: C36.2, J9.3
unnamed: C37.2, J9.4
unnamed: C38.2, J9.6
unnamed: C39.2, J9.7
unnamed: C40.2, J9.9
unnamed: C41.2, J9.10
unnamed: C42.2, J9.12
unnamed: D8.A, R20.1
unnamed: D7.A, R19.1
unnamed: JP11.2, JP12.1
unnamed: JP10.2, JP12.3
unnamed: JP10.1, R23.2
unnamed: JP11.1, R24.2
unnamed: C49.2, J12.1
unnamed: C50.2, J12.3
unnamed: C51.2, J12.4
unnamed: C52.2, J12.6
unnamed: C53.2, J12.7
unnamed: C54.2, J12.9
unnamed: C55.2, J12.10
unnamed: C56.2, J12.12
unnamed: D10.A, R26.1
unnamed: D9.A, R25.1
unnamed: JP14.2, JP15.1
unnamed: JP13.2, JP15.3
unnamed: JP13.1, R29.2
unnamed: JP14.1, R30.2
unnamed: C63.2, J15.1
unnamed: C64.2, J15.3
unnamed: C65.2, J15.4
unnamed: C66.2, J15.6
unnamed: C67.2, J15.7
unnamed: C68.2, J15.9
unnamed: C69.2, J15.10
unnamed: C70.2, J15.12
unnamed: D12.A, R32.1
unnamed: D11.A, R31.1
unnamed: JP17.2, JP18.1
unnamed: JP16.2, JP18.3
unnamed: JP16.1, R35.2
unnamed: JP17.1, R36.2
unnamed: C77.2, J18.1
unnamed: C78.2, J18.3
unnamed: C79.2, J18.4
unnamed: C80.2, J18.6
unnamed: C81.2, J18.7
unnamed: C82.2, J18.9
unnamed: C83.2, J18.10
unnamed: C84.2, J18.12
unnamed: D14.A, R38.1
unnamed: D13.A, R37.1
unnamed: JP20.2, JP21.1
unnamed: JP19.2, JP21.3
unnamed: JP19.1, R41.2
unnamed: JP20.1, R42.2
unnamed: C91.2, J21.1
unnamed: C92.2, J21.3
unnamed: C93.2, J21.4
unnamed: C94.2, J21.6
unnamed: C95.2, J21.7
unnamed: C96.2, J21.9
unnamed: C97.2, J21.10
unnamed: C98.2, J21.12
unnamed: D16.A, R44.1
unnamed: D15.A, R43.1
unnamed: JP23.2, JP24.1
unnamed: JP22.2, JP24.3
unnamed: JP22.1, R47.2
unnamed: JP23.1, R48.2
unnamed: C105.2, J24.1
unnamed: C106.2, J24.3
unnamed: C107.2, J24.4
unnamed: C108.2, J24.6
unnamed: C109.2, J24.7
unnamed: C110.2, J24.9
unnamed: C111.2, J24.10
unnamed: C112.2, J24.12
unnamed: D18.A, R50.1
unnamed: D17.A, R49.1
unnamed: JP26.2, JP27.1
unnamed: JP25.2, JP27.3
unnamed: JP25.1, R53.2
unnamed: JP26.1, R54.2
unnamed: C119.2, J27.1
unnamed: C120.2, J27.3
unnamed: C121.2, J27.4
unnamed: C122.2, J27.6
unnamed: C123.2, J27.7
unnamed: C124.2, J27.9
unnamed: C125.2, J27.10
unnamed: C126.2, J27.12
unnamed: D20.A, R56.1
unnamed: D19.A, R55.1
unnamed: JP29.2, JP30.1
unnamed: JP28.2, JP30.3
unnamed: JP28.1, R59.2
unnamed: JP29.1, R60.2
unnamed: C133.2, J30.1
unnamed: C134.2, J30.3
unnamed: C135.2, J30.4
unnamed: C136.2, J30.6
unnamed: C137.2, J30.7
unnamed: C138.2, J30.9
unnamed: C139.2, J30.10
unnamed: C140.2, J30.12
unnamed: D22.A, R62.1
unnamed: D21.A, R61.1
unnamed: JP32.2, JP33.1
unnamed: JP31.2, JP33.3
unnamed: JP31.1, R65.2
unnamed: JP32.1, R66.2
unnamed: C147.2, J33.1
unnamed: C148.2, J33.3
unnamed: C149.2, J33.4
unnamed: C150.2, J33.6
unnamed: C151.2, J33.7
unnamed: C152.2, J33.9
unnamed: C153.2, J33.10
unnamed: C154.2, J33.12
unnamed: D24.A, R68.1
unnamed: D23.A, R67.1
unnamed: JP35.2, JP36.1
unnamed: JP34.2, JP36.3
unnamed: JP34.1, R71.2
unnamed: JP35.1, R72.2
unnamed: C161.2, J36.1
unnamed: C162.2, J36.3
unnamed: C163.2, J36.4
unnamed: C164.2, J36.6
unnamed: C165.2, J36.7
unnamed: C166.2, J36.9
unnamed: C167.2, J36.10
unnamed: C168.2, J36.12
unnamed: D26.A, R74.1
unnamed: D25.A, R73.1
unnamed: JP38.2, JP39.1
unnamed: JP37.2, JP39.3
unnamed: JP37.1, R77.2
unnamed: JP38.1, R78.2
unnamed: C175.2, J39.1
unnamed: C176.2, J39.3
unnamed: C177.2, J39.4
unnamed: C178.2, J39.6
unnamed: C179.2, J39.7
unnamed: C180.2, J39.9
unnamed: C181.2, J39.10
unnamed: C182.2, J39.12
unnamed: D28.A, R80.1
unnamed: D27.A, R79.1
unnamed: JP41.2, JP42.1
unnamed: JP40.2, JP42.3
unnamed: JP40.1, R83.2
unnamed: JP41.1, R84.2
unnamed: C189.2, J42.1
unnamed: C190.2, J42.3
unnamed: C191.2, J42.4
unnamed: C192.2, J42.6
unnamed: C193.2, J42.7
unnamed: C194.2, J42.9
unnamed: C195.2, J42.10
unnamed: C196.2, J42.12
RST: S1.3, S1.4, U$1.P$3
RST1: S2.3, S2.4, U$10.P$3
RST2: S3.3, S3.4, U$19.P$3
RST3: S4.3, S4.4, U$28.P$3
RST4: S5.3, S5.4, U$37.P$3
RST5: S6.3, S6.4, U$46.P$3
RST6: S7.3, S7.4, U$55.P$3
RST7: S8.3, S8.4, U$64.P$3
RST8: S9.3, S9.4, U$73.P$3
RST9: S10.3, S10.4, U$82.P$3
RST10: S11.3, S11.4, U$91.P$3
RST11: S12.3, S12.4, U$100.P$3
RST12: S13.3, S13.4, U$109.P$3
RST13: S14.3, S14.4, U$118.P$3
RTS: U1.4, U$1.P$59
RTS1: U2.4, U$10.P$59
RTS2: U3.4, U$19.P$59
RTS3: U4.4, U$28.P$59
RTS4: U5.4, U$37.P$59
RTS5: U6.4, U$46.P$59
RTS6: U7.4, U$55.P$59
RTS7: U8.4, U$64.P$59
RTS8: U9.4, U$73.P$59
RTS9: U10.4, U$82.P$59
RTS10: U11.4, U$91.P$59
RTS11: U12.4, U$100.P$59
RTS12: U13.4, U$109.P$59
RTS13: U14.4, U$118.P$59
RXI: D1.C, U1.9, U$1.P$58
RXI1: D4.C, U2.9, U$10.P$58
RXI2: D6.C, U3.9, U$19.P$58
RXI3: D8.C, U4.9, U$28.P$58
RXI4: D10.C, U5.9, U$37.P$58
RXI5: D12.C, U6.9, U$46.P$58
RXI6: D14.C, U7.9, U$55.P$58
RXI7: D16.C, U8.9, U$64.P$58
RXI8: D18.C, U9.9, U$73.P$58
RXI9: D20.C, U10.9, U$82.P$58
RXI10: D22.C, U11.9, U$91.P$58
RXI11: D24.C, U12.9, U$100.P$58
RXI12: D26.C, U13.9, U$109.P$58
RXI13: D28.C, U14.9, U$118.P$58
SCL: J1.4, R6.1, U$1.P$34
SCL1: J4.4, R11.1, U$10.P$34
SCL2: J8.4, R17.1, U$19.P$34
SCL3: J11.4, R23.1, U$28.P$34
SCL4: J14.4, R29.1, U$37.P$34
SCL5: J17.4, R35.1, U$46.P$34
SCL6: J20.4, R41.1, U$55.P$34
SCL7: J23.4, R47.1, U$64.P$34
SCL8: J26.4, R53.1, U$73.P$34
SCL9: J29.4, R59.1, U$82.P$34
SCL10: J32.4, R65.1, U$91.P$34
SCL11: J35.4, R71.1, U$100.P$34
SCL12: J38.4, R77.1, U$109.P$34
SCL13: J41.4, R83.1, U$118.P$34
SDA: J1.3, R7.1, U$1.P$35
SDA1: J4.3, R12.1, U$10.P$35
SDA2: J8.3, R18.1, U$19.P$35
SDA3: J11.3, R24.1, U$28.P$35
SDA4: J14.3, R30.1, U$37.P$35
SDA5: J17.3, R36.1, U$46.P$35
SDA6: J20.3, R42.1, U$55.P$35
SDA7: J23.3, R48.1, U$64.P$35
SDA8: J26.3, R54.1, U$73.P$35
SDA9: J29.3, R60.1, U$82.P$35
SDA10: J32.3, R66.1, U$91.P$35
SDA11: J35.3, R72.1, U$100.P$35
SDA12: J38.3, R78.1, U$109.P$35
SDA13: J41.3, R84.1, U$118.P$35
TXO: D2.C, U1.8, U$1.P$57
TXO1: D3.C, U2.8, U$10.P$57
TXO2: D5.C, U3.8, U$19.P$57
TXO3: D7.C, U4.8, U$28.P$57
TXO4: D9.C, U5.8, U$37.P$57
TXO5: D11.C, U6.8, U$46.P$57
TXO6: D13.C, U7.8, U$55.P$57
TXO7: D15.C, U8.8, U$64.P$57
TXO8: D17.C, U9.8, U$73.P$57
TXO9: D19.C, U10.8, U$82.P$57
TXO10: D21.C, U11.8, U$91.P$57
TXO11: D23.C, U12.8, U$100.P$57
TXO12: D25.C, U13.8, U$109.P$57
TXO13: D27.C, U14.8, U$118.P$57

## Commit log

2020-08-15 Changed the HDMI connector footprint
2020-08-18 Added the production panel
2020-09-08 Added the license

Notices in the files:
parts and their libraries:
SparkFun-Aesthetics: Licensing: Creative Commons ShareAlike 4.0 International - https://creativecommons.org/licenses/by-sa/4.0
SparkFun-Aesthetics: Released under the Creative Commons Attribution Share-Alike 4.0 License
SparkFun-Aesthetics: https://creativecommons.org/licenses/by-sa/4.0
